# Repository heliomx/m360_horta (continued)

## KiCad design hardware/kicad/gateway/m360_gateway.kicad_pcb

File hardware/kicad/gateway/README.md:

# PCB — Gateway MQTT M360 (rev A)

Placa-mãe (*carrier*) para o **Gateway Manejo360**, derivada diretamente do firmware
[`src/DRY/gateway/libDryGatewayMqtt.cpp`](../../../src/DRY/gateway/libDryGatewayMqtt.cpp)
e das definições em [`lib/M360-DRY/src/M360Leds.h`](../../../lib/M360-DRY/src/M360Leds.h)
e no `platformio.ini` (env `d1_mini_gateway`).

O ESP8266 e o rádio **não** são soldados: ambos entram em soquetes fêmea, permitindo
troca em campo sem ferro de solda.

| Arquivo | Conteúdo |
|---|---|
| `m360_gateway.kicad_pro` / `.kicad_sch` / `.kicad_pcb` | Projeto KiCad (formato nativo S-expression) |
| `m360_gateway_esquematico.pdf` | Esquemático em PDF |
| `m360_gateway_bom.csv` | Lista de materiais |

**Estado:** ERC 0 violações · DRC 0 erros (ver *Pendências* no fim).

---

## Requisitos extraídos do firmware

| Sinal | Pino D1 mini | GPIO | Origem no código |
|---|---|---|---|
| RF24 CE | D4 | 2 | `platformio.ini` → `-D MY_RF24_CE_PIN=2` |
| RF24 CSN | D8 | 15 | `platformio.ini` → `-D MY_RF24_CSN_PIN=15` |
| RF24 SCK / MISO / MOSI | D5 / D6 / D7 | 14 / 12 / 13 | HW SPI do ESP8266 (MySensors) |
| LED vermelho (ERRO) | D2 | 4 | `M360Leds.h` → `LED_RED` |
| LED verde (OK) | D1 | 5 | `M360Leds.h` → `LED_GREEN` |
| LED amarelo (TX/AP) | D0 | 16 | `M360Leds.h` → `LED_YELLOW` |
| Entrada de configuração | A0 | ADC | `M360Leds.h` → `RESET_PIN`; `isA0Low()` em `libDryGatewayMqtt.cpp:37` |

Os LEDs são **ativos em nível alto** (`digitalWrite(pin, HIGH)` acende — ver
`M360Leds.cpp:47`), logo o ânodo vai ao GPIO e o cátodo ao GND via resistor.

---

## Componentes

| Ref | Valor | Footprint | Função |
|---|---|---|---|
| **U1** | WEMOS D1 mini | `RF_Module:WEMOS_D1_mini_light` | ESP8266 — soldar **duas barras fêmea 1x8** no lugar do módulo |
| **U2** | nRF24L01+ | `PinSocket_2x04_P2.54mm_Vertical` | Soquete do rádio |
| **U3** | AMS1117-3.3 | SOT-223 | LDO **dedicado ao rádio** |
| **J1** | 5V IN | Bornier 1x02 P5.00 | Alimentação 5 V |
| **J2** | EXPANSÃO | Pin header 1x06 | 5V · 3V3 · GND · TX · RX · D3 |
| **J3** | IRQ SEL | Pin header 1x02 | Jumper opcional IRQ(nRF24) → D3 |
| **F1** | PTC 500 mA | Fuse Bourns MF-RG500 | Proteção de sobrecorrente |
| **D1** | 1N5819 | DO-41 | Proteção contra inversão de polaridade |
| **D2 / D4 / D3** | LED verm. / verde / amar. | LED 3 mm | ERRO / OK / TX-AP |
| **R1 / R3 / R2** | 470 Ω | Axial 1/4 W | Limitação dos LEDs |
| **R4** | 10 kΩ | Axial 1/4 W | **Pull-up de A0** (crítico — ver abaixo) |
| **R5** | 10 kΩ | Axial 1/4 W | **Pull-down de GPIO15/CSN** (boot) |
| **C1** | 470 µF / 16 V | Radial D8 | Reservatório da entrada 5 V |
| **C2** | 100 nF | Disco 5 mm | Entrada do LDO |
| **C5 / C3** | 10 µF / 100 µF | Radial D8 | Saída do LDO (3V3_RF) |
| **C4** | 100 nF | Disco 5 mm | Desacoplamento junto ao rádio |
| **SW1** | CFG / AP | Push 6 mm | Curto de A0 ao GND → modo configuração |
| **H1–H4** | — | Furo M3 (3,2 mm) | Fixação |

---

## Três decisões de projeto que valem explicação

### 1. R4 (10 k de A0 para 3V3) não é opcional

`isA0Low()` lê A0 duas vezes e considera "modo manutenção" se a média ficar
abaixo de 400 (de 1023). No D1 mini o pino A0 do header entra por um divisor
220 k / 100 k até o ADC do ESP. **Com A0 flutuando o ADC lê perto de zero**, o
firmware entenderia isso como pedido de modo AP e a placa **nunca sairia do
portal de configuração**.

Com R4 = 10 k para 3V3, o ADC fica em ≈1,0 V (≈1023) em repouso e vai a 0 quando
SW1 é pressionado. É o que dá sentido ao caminho `else if (isA0Low(RESET_PIN))`
em `libDryGatewayMqtt.cpp:251`.

### 2. LDO dedicado (U3) para o rádio

O `platformio.ini` usa `-D MY_RF24_PA_LEVEL=RF24_PA_HIGH`. Com um nRF24L01+
"nu" o consumo é modesto (~13 mA), mas com a variante **PA+LNA** — a esperada
num gateway central — o pico de TX passa de 100 mA e o regulador embarcado do
D1 mini fica no limite, provocando resets e perda de pacotes. U3 alimenta apenas
o rádio, com C3/C5/C4 no ponto de uso. A rede `+3V3_RF` é separada da `+3V3`
(que só alimenta R4 e o pino 3V3 do header de expansão); os GNDs são comuns.

### 3. R5 (10 k de CSN para GND)

GPIO15 precisa estar em nível baixo no boot do ESP8266. Como o CSN do nRF24
fica em alto-Z antes do firmware assumir o pino, R5 garante o *strap* correto.

**O que foi deliberadamente omitido:** pull-up em GPIO2/CE (o D1 mini já tem, via
o LED onboard) e botão de reset + pull-up de RST (o próprio módulo tem os dois, e
com o D1 mini em soquete o botão fica acessível por cima). O pino RST de U1 está
marcado como *no-connect* no esquemático.

---

## Layout

Placa de **100 × 70 mm**, 2 camadas, planos de GND em ambas as faces.

```
        ┌──────────────────────────────────────────────────┐
  y=14  │ J1 → F1 → D1 → C1 → C2 → U3 → C5 → C3            │  cadeia de energia
        │                                                  │
  y=26  │            R5      ┌───── U2 (nRF24) ─────►      │  antena p/ direita
  y=32  │  ┌──── U1 ────┐    │ SPI curto (4 trilhas)       │
  y=44  │  │  D1 mini   │ R4 │                    SW1      │
  y=58  │  └────────────┘    │                             │
  y=66  │  R1  R3  R2        │            J2 (expansão)    │
  y=74  │  D2  D4  D3        │                       J3    │
        └──────────────────────────────────────────────────┘
```

- **U1 girado 180°** para que a coluna de pinos D5–D8 (SPI) fique voltada ao rádio.
  Isso reduz as quatro trilhas SPI de ~50 mm para ~25 mm cada. Consequência: o
  conector USB do D1 mini aponta para a borda inferior (marcado na serigrafia).
- A camada superior concentra energia (5 V, 3V3, 3V3_RF) e a inferior os sinais SPI.
- O footprint do D1 mini traz uma **zona de exclusão de cobre** (região da antena do
  ESP-12, x 15,75–41,35 / y 51,4–58,2). O roteamento a contorna — se for mover peças,
  respeite essa área.
- Os planos de GND têm um **recorte em x 84–99,5 / y 19–41**, sob a ponta do módulo
  de rádio, para não degradar a antena.

### Regras de projeto

| Parâmetro | Valor |
|---|---|
| Isolação mínima | 0,25 mm |
| Trilha padrão / sinal | 0,35 mm |
| Trilha de 3V3 | 0,5 mm |
| Trilha de 5 V / 3V3_RF | 0,8 mm |
| Via | 0,8 mm (furo 0,4 mm) |
| Vias de costura GND | 0,6 mm (furo 0,3 mm) |

Compatível com o processo mais barato de qualquer fab (JLCPCB/PCBWay classe 2).

---

## Montagem e uso

1. Alimentar J1 com **5 V regulados** (fonte de 5 V/1 A). D1 protege contra inversão;
   F1 abre em curto.
2. O D1 mini entra nas barras fêmea com o **USB voltado para a borda inferior**.
3. O nRF24 entra em U2 com a **antena apontando para a borda direita** da placa.
4. `SW1` pressionado durante o boot (ou config inválida) → modo AP `M360-Config`
   em `192.168.4.1`.
5. LEDs, conforme `updateLEDStatus()`:
   - verde aceso = WiFi + MQTT OK
   - amarelo piscando 400 ms = WiFi OK, sem MQTT
   - amarelo piscando 200 ms = modo AP
   - vermelho piscando 300 ms = sem WiFi
6. `J3` fechado liga o IRQ do rádio ao D3 (GPIO0). **Deixe aberto** — o firmware atual
   não usa interrupção e GPIO0 é pino de *strap* de boot.

---

## Pendências antes de fabricar

1. **Preencher as zonas**: abra o `.kicad_pcb` no KiCad e tecle `B`. O backend usado
   aqui não preenche zonas, então as 36 vias de costura aparecem como
   *via dangling* no DRC até o primeiro preenchimento.
2. **Serigrafia**: 3 avisos cosméticos de DRC (texto de referência próximo à borda /
   sobre máscara). Reposicione com *Autoposition Field* no KiCad.
3. **Conferir o módulo de rádio físico**: o footprint é apenas o soquete 2x4. Confirme
   que o corpo do seu módulo (≈15,3 × 29 mm) cabe na área reservada e que a antena
   fica sobre o recorte dos planos.
4. **Se usar nRF24 PA+LNA**: considere subir C3 para 220 µF e conferir se o AMS1117
   dissipa bem (5 V → 3,3 V a 120 mA ≈ 0,2 W, ok em SOT-223).

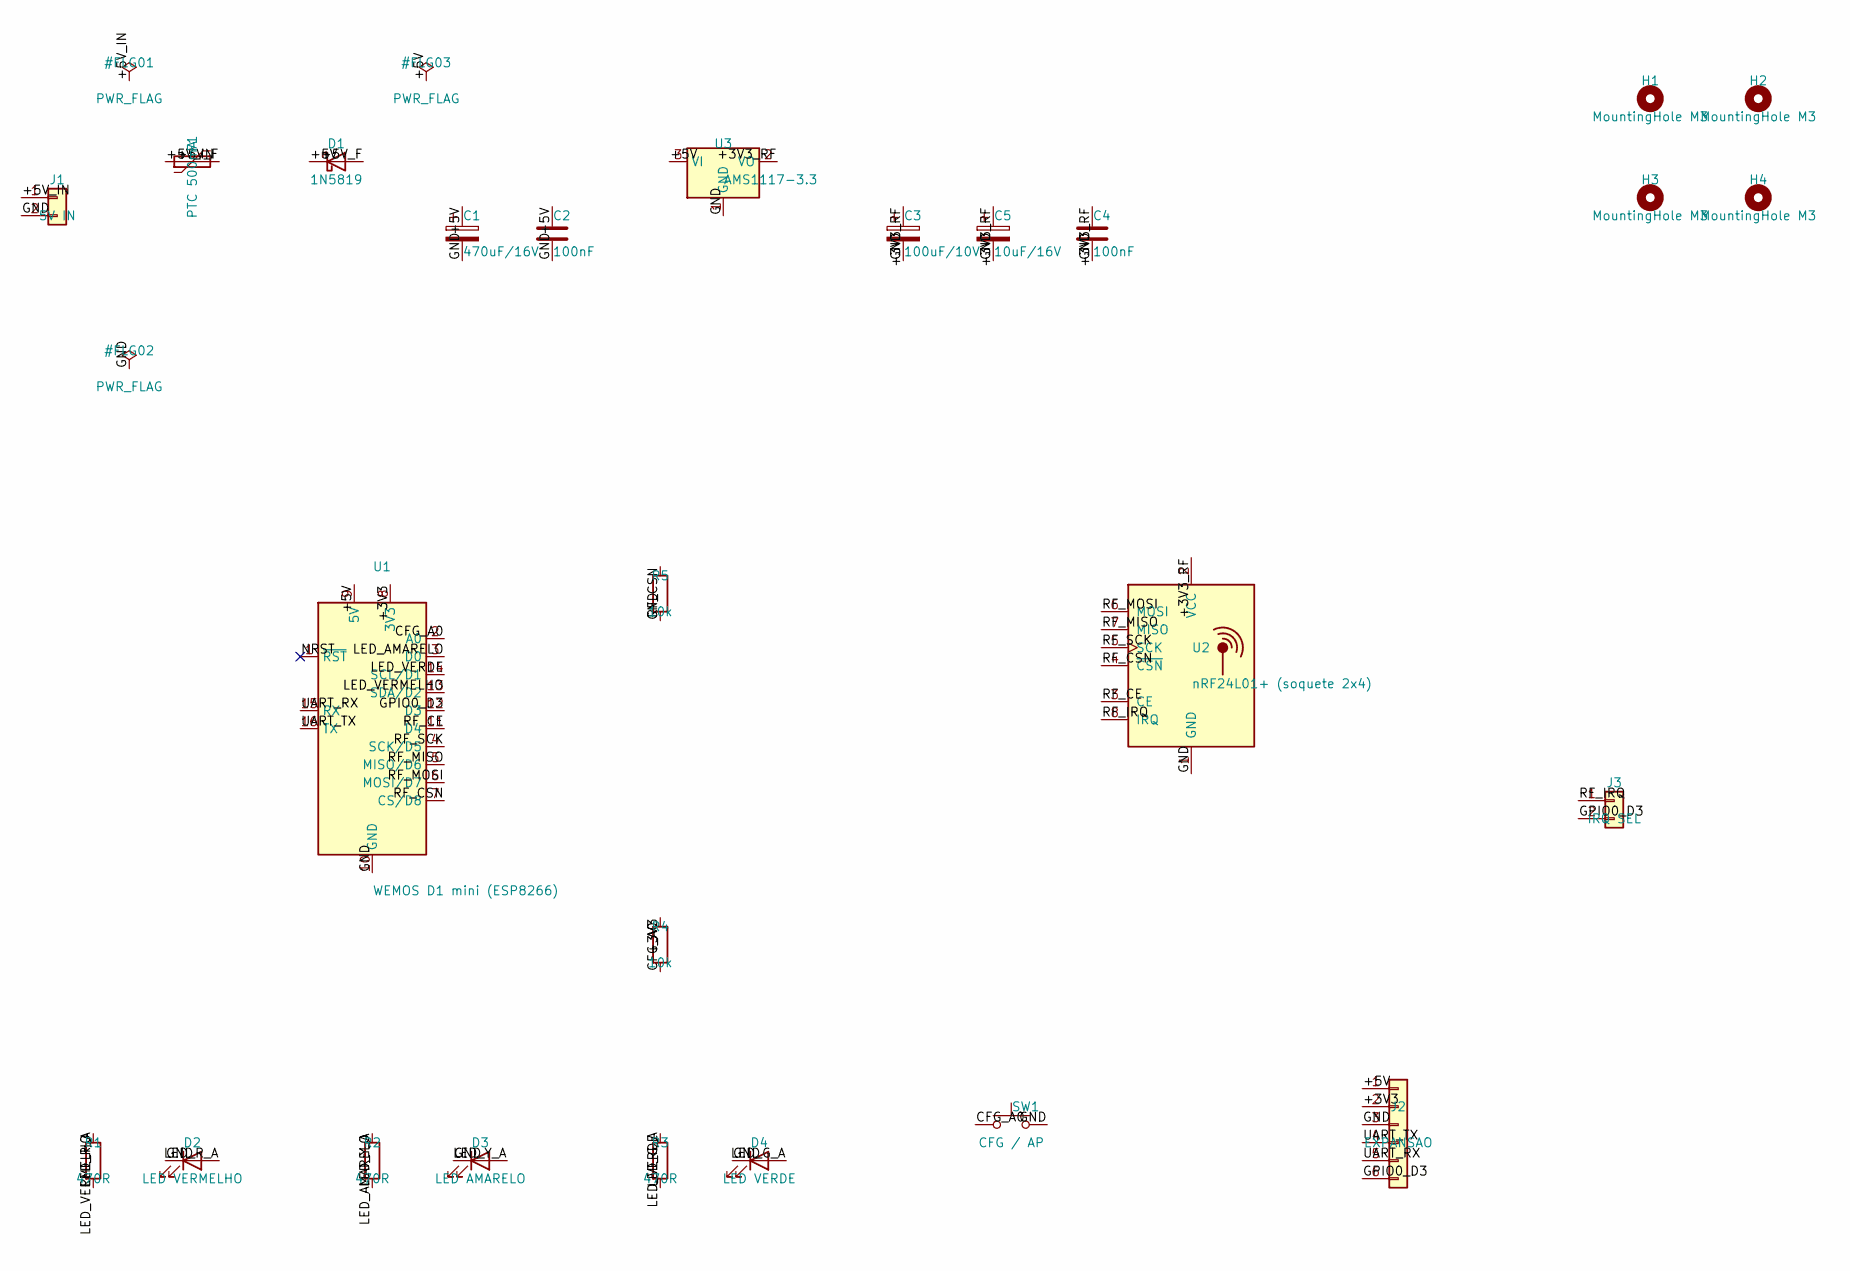
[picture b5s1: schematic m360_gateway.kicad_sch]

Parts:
C1: 470uF/16V; CP_Radial_D8.0mm_P3.50mm
C2, C4: 100nF; C_Disc_D5.0mm_W2.5mm_P5.00mm
C3: 100uF/10V; CP_Radial_D8.0mm_P3.50mm
C5: 10uF/16V; CP_Radial_D8.0mm_P3.50mm
D1: 1N5819; D_DO-41_SOD81_P10.16mm_Horizontal
D2: LED VERMELHO; LED_D3.0mm
D3: LED AMARELO; LED_D3.0mm
D4: LED VERDE; LED_D3.0mm
F1: PTC 500mA; Fuse_Bourns_MF-RG500
H1, H2, H3, H4: MountingHole M3; MountingHole_3.2mm_M3
J1: 5V IN; TerminalBlock_MaiXu_MX126-5.0-02P_1x02_P5.00mm
J2: EXPANSAO; PinHeader_1x06_P2.54mm_Vertical
J3: IRQ SEL; PinHeader_1x02_P2.54mm_Vertical
R1, R2, R3: 470R; R_Axial_DIN0207_L6.3mm_D2.5mm_P7.62mm_Horizontal
R4, R5: 10k; R_Axial_DIN0207_L6.3mm_D2.5mm_P7.62mm_Horizontal
SW1: CFG / AP; SW_PUSH_6mm
U1: WEMOS D1 mini (ESP8266); WEMOS_D1_mini_light
U2: nRF24L01+ (soquete 2x4); PinSocket_2x04_P2.54mm_Vertical
U3: AMS1117-3.3; SOT-223-3_TabPin2

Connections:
+3V3: J2.2, R4.1, U1.8 (3V3)
+3V3_RF: C3.1, C4.1, C5.1, U2.2 (VCC), U3.2 (VO)
+5V: C1.1, C2.1, D1.1 (K), J2.1, U1.9 (5V), U3.3 (VI)
+5V_F: D1.2 (A), F1.2
+5V_IN: F1.1, J1.1
CFG_A0: R4.2, SW1.1, U1.2 (A0)
GND: C1.2, C2.2, C3.2, C4.2, C5.2, D2.1 (K), D3.1 (K), D4.1 (K), J1.2, J2.3, R5.2, SW1.2, U1.10 (GND), U2.1 (GND), U3.1 (GND)
GPIO0_D3: J2.6, J3.2, U1.12 (D3)
LED_AMARELO: R2.1, U1.3 (D0)
LED_G_A: D4.2 (A), R3.2
LED_R_A: D2.2 (A), R1.2
LED_VERDE: R3.1, U1.14 (SCL/D1)
LED_VERMELHO: R1.1, U1.13 (SDA/D2)
LED_Y_A: D3.2 (A), R2.2
NRST: U1.1 (~RST)
RF_CE: U1.11 (D4), U2.3 (CE)
RF_CSN: R5.1, U1.7 (CS/D8), U2.4 (~CSN)
RF_IRQ: J3.1, U2.8 (IRQ)
RF_MISO: U1.5 (MISO/D6), U2.7 (MISO)
RF_MOSI: U1.6 (MOSI/D7), U2.6 (MOSI)
RF_SCK: U1.4 (SCK/D5), U2.5 (SCK)
UART_RX: J2.5, U1.15 (RX)
UART_TX: J2.4, U1.16 (TX)

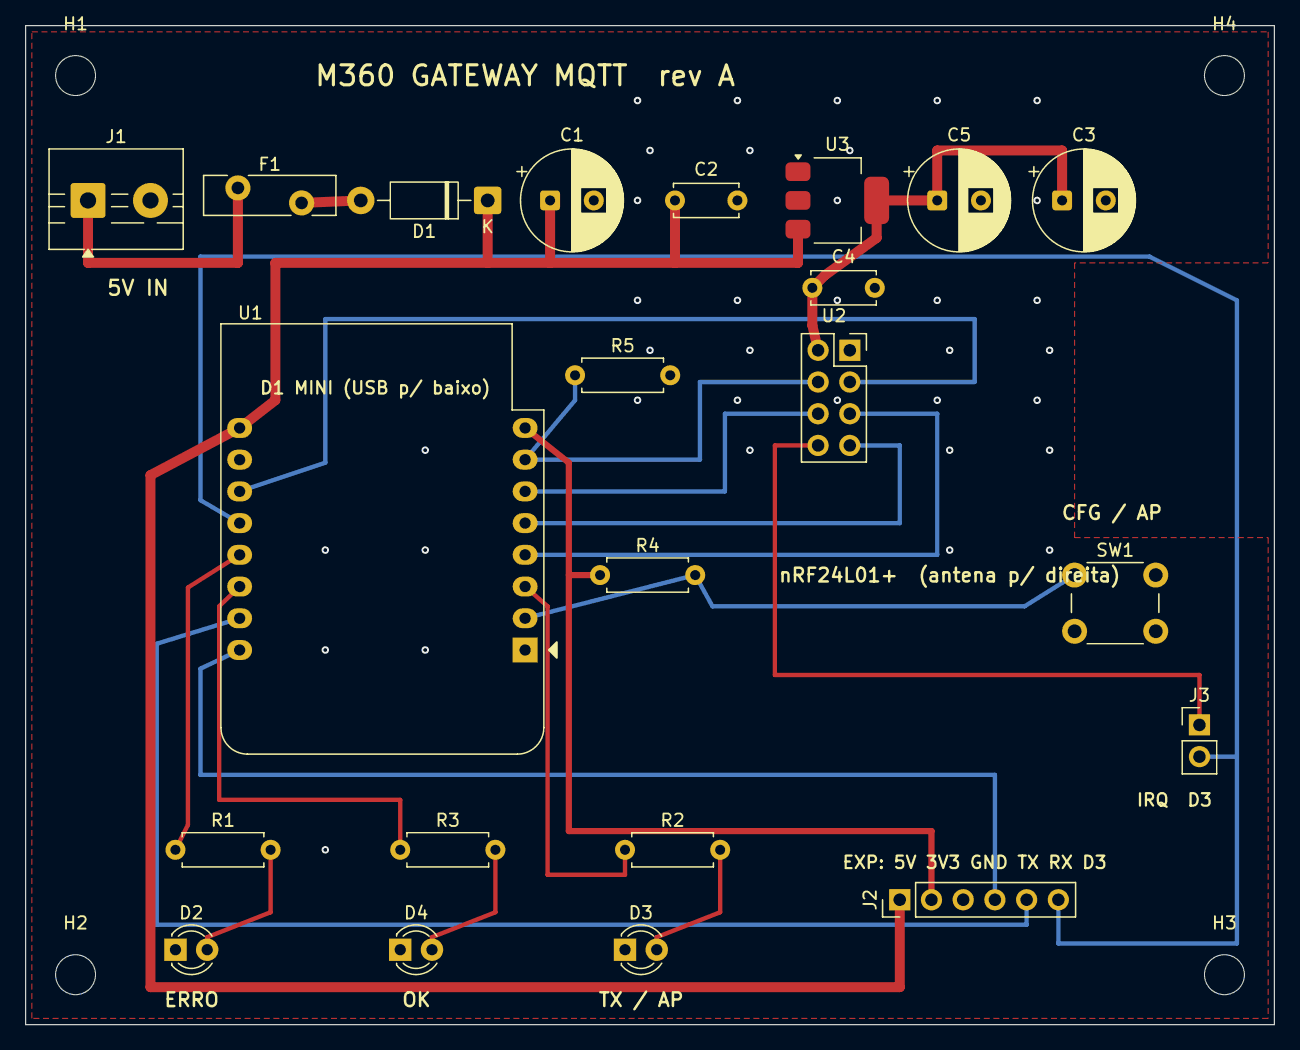
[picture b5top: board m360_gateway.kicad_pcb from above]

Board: 2 copper layers, 100.0 x 80.0 mm, 26 parts (0 on the bottom side), 22 nets.

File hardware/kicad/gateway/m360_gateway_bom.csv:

value,footprint,quantity,references
MountingHole M3,MountingHole:MountingHole_3.2mm_M3,4,"['H2', 'H1', 'H4', 'H3']"
1N5819,Diode_THT:D_DO-41_SOD81_P10.16mm_Horizontal,1,['D1']
PTC 500mA,Fuse:Fuse_Bourns_MF-RG500,1,['F1']
CFG / AP,Button_Switch_THT:SW_PUSH_6mm,1,['SW1']
WEMOS D1 mini (ESP8266),RF_Module:WEMOS_D1_mini_light,1,['U1']
470R,Resistor_THT:R_Axial_DIN0207_L6.3mm_D2.5mm_P7.62mm_Horizontal,3,"['R3', 'R2', 'R1']"
AMS1117-3.3,Package_TO_SOT_SMD:SOT-223-3_TabPin2,1,['U3']
LED AMARELO,LED_THT:LED_D3.0mm,1,['D3']
10k,Resistor_THT:R_Axial_DIN0207_L6.3mm_D2.5mm_P7.62mm_Horizontal,2,"['R5', 'R4']"
nRF24L01+ (soquete 2x4),Connector_PinSocket_2.54mm:PinSocket_2x04_P2.54mm_Vertical,1,['U2']
LED VERMELHO,LED_THT:LED_D3.0mm,1,['D2']
EXPANSAO,Connector_PinHeader_2.54mm:PinHeader_1x06_P2.54mm_Vertical,1,['J2']
100uF/10V,Capacitor_THT:CP_Radial_D8.0mm_P3.50mm,1,['C3']
100nF,Capacitor_THT:C_Disc_D5.0mm_W2.5mm_P5.00mm,2,"['C2', 'C4']"
LED VERDE,LED_THT:LED_D3.0mm,1,['D4']
IRQ SEL,Connector_PinHeader_2.54mm:PinHeader_1x02_P2.54mm_Vertical,1,['J3']
470uF/16V,Capacitor_THT:CP_Radial_D8.0mm_P3.50mm,1,['C1']
5V IN,TerminalBlock:TerminalBlock_MaiXu_MX126-5.0-02P_1x02_P5.00mm,1,['J1']
10uF/16V,Capacitor_THT:CP_Radial_D8.0mm_P3.50mm,1,['C5']

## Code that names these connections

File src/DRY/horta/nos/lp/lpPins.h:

/*
 * lpPins.h — Pinagem fixa da placa M360-LP (Pro Mini 3,3 V / 8 MHz)
 *
 * Fonte: hardware/m360-lp/M360-LP.kicad_sch (netlist conferida em 2026-10-14)
 * e hardware/ARQUITETURA_FAMILIA.md §4.3. Nada aqui varia entre nós: o que
 * varia (sensores presentes, rótulos, child IDs, alimentação) fica em
 * config/<nó>/nodeConfig.h.
 *
 * Pinos do rádio (DIO0=D2, DIO1=D9, NSS=D10, RESET=D8; nRF24 legado CE=D2,
 * CSN=D10) são do MySensors e entram pelo platformio.ini ([lp_base]) — R1.
 */

#pragma once
#include <Arduino.h>

// ===== TRILHO CHAVEADO VSW (3,3 V dos sensores, pull-ups e par marrom) =====
// P-MOSFET high-side (Q2) com gate em 100 kΩ para o 3V3: LOW liga, HIGH desliga.
// Desligado no boot por hardware; o firmware só confirma.
#define LP_PIN_VSW_EN      4
#define LP_VSW_ON          LOW
#define LP_VSW_OFF         HIGH

// ===== 74HC4051 (8 canais de solo em A0) =====
#define LP_PIN_MUX_S0      5
#define LP_PIN_MUX_S1      6
#define LP_PIN_MUX_S2      7
#define LP_PIN_MUX_OUT     A0

// ===== DIGITAIS DE CAMPO (porta J2 CLIMA/AUX) =====
#define LP_PIN_ONEWIRE     A1   // DS18B20, pull-up 4,7 kΩ para o VSW na placa
#define LP_PIN_DHT         A2   // DHT11/22, pull-up 10 kΩ para o VSW na placa
// A4/A5 = SDA/SCL (pull-ups 3,3 kΩ para o VSW). Sem driver ainda — ver README.

// ===== OUTROS =====
#define LP_PIN_REED        3    // reed switch SW1 para GND (INT1), INPUT_PULLUP — nunca saída.
                                // Ímã: força leitura e envio de todos os children.
#define LP_PIN_VBAT        A6   // divisor 2 MΩ / 1 MΩ permanente + 100 nF
#define LP_VBAT_DIVIDER    3.0f // VBAT = 3 × V(A6)

// ===== CÓDIGOS DE FONTE NO CAMPO `pin` DE M360ItemDef =====
// Mesma convenção de pino virtual do Nó 99 (R7): o motor não faz pinMode em
// nada — setupPins() é omitido — e lpReadSource() despacha pelo código.
#define LP_SRC_SOIL_BASE   100               // canal 0..7 do 74HC4051
#define LP_SRC_SOIL(ch)    (LP_SRC_SOIL_BASE + (ch))
#define LP_IS_SOIL(p)      ((p) >= LP_SRC_SOIL_BASE && (p) < LP_SRC_SOIL_BASE + 8)
#define LP_SOIL_CH(p)      ((uint8_t)((p) - LP_SRC_SOIL_BASE))
#define LP_SRC_DHT_TEMP    120
#define LP_SRC_DHT_HUM     121
#define LP_SRC_DS18B20     130

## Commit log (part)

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2026-06-18 primeiro commit
2026-06-20 feat: add node template driver structure, 80nodeAqua documentation, and boilerplate configuration files
2026-06-21 feat: implement hardware documentation and node logic for 80nodeAqua and 99nodeReles using the DRY library structure
2026-06-21 work: alterações feitas pelo Codex
2026-06-21 refactor: integrate M360Gateway library into gateway and node implementations for standardized operation
2026-06-21 feat: implement LibDRY node and gateway scaffolding with sensor driver templates and configuration utilities
2026-06-23 feat: initialize node structure with documentation, configuration files, and standard sensor drivers
2026-06-26 docs: add planning, testing protocols, and initial Node-RED network map for MVP development
2026-06-26 feat: implement M360Node lifecycle management library for MySensors-based nodes with power profiling support
2026-06-26 feat: initialize Node-RED MQTT workflows, sensor drivers, and project documentation
2026-06-26 feat: add sensor driver implementation for water metrics and initialize Node-RED network mapping files
2026-06-29 Mudanças aplicadas
    lib/M360-DRY/src/M360Node.cpp — handleMessage
    Bug 1 — Echo guard (linha 141): adicionado if (msg.isEcho()) return; antes de qualquer processamento. Sem isso, V_STATUS com requestEcho=true acionaria _writeCb duas vezes no nó 99 (relés).
    Bug 2 — Buffer overflow (linha 182–185): o char buf[24] era pequeno demais (MAX_PAYLOAD_SIZE = 25). Agora é char buf[25] com guard if (msg.getLength() >= 25) return; antes do getString.
    Bug 3 — Confirmação de intervalo (linha 157–160): send() e Serial.print movidos para fora do bloco if (iv >= MIN && iv <= MAX). O gateway agora sempre recebe o valor vigente — se mandou 9999, recebe 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
2026-06-29 feat: nó repetidos; lib/M360-DRY/src/M360Node.h — M360_REPEATER adicionado ao enum M360PowerProfile com comentário explicando requisitos e incompatibilidades.
    lib/M360-DRY/src/M360Node.cpp:
    - begin(): case M360_REPEATER: suffix = " [REP]" — o nome do nó no gateway fica "99nodeReles [REP]"
    - process(): condição || _profile == M360_REPEATER — compartilha o bloco millis-timer do ALWAYS_ON; o MySensors cuida do forwarding dentro do wait(50) de forma transparente
    platformio.ini — novo [env:nano_99reles_rep] fora de default_envs; para flashar: pio run -e nano_99reles_rep -t upload
    99nodeReles.cpp — instância do M360Node agora usa #ifdef MY_REPEATER_FEATURE para selecionar M360_RE
2026-06-29 feat: add M360Translator class for MySensors and JSON payload serialization/deserialization
2026-06-29 feat: implement M360Translator to handle MySensors and JSON message conversion
